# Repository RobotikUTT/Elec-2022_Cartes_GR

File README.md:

# Elec-2022_Cartes_GR

Circuits imprimés pour le Gros Robot de la Coupe de France de Robotique 2022

## PCB Arduino Mega (PCB_Mega)
Shield pour Arduino Mega 2560.
Alimentée en 5V par un bornier à vis.

**Comprends :**
- Port série pour la communication avec la Nano
- Ports séries Servos (XL320 + AX-12A)
- Sorties logiques moteurs roues
- Sorties pompes à vide
- Entrées Roues Codeuses
- Entrées analogiques courant pompes à vide
- Entrées Tirette et Interrupteur de sélection du côté
- Leds de Status Rouge, Verte et Bleue
- 10 GPIO supplémentaires non-utilisés

___

## PCB Arduino Nano (PCB_Nano)
Module hôte pour Arduino Nano.
Alimentée en 5V par un bornier à vis.

**Comprends :**
- Port série pour communication avec la Mega
- Port I2C pour écran LCD
- Entrées/Sorties Echos et Triggers pour les sonars
- 6 GPIO supplémentaires non-utilisés

## PCB Alimentation (PCB_Power)
Module d'alimentation pour le Gros Robot.

**Rails fournis :**
- 5V (2A max) : Arduinos Mega et Nano, pompes à vide et écran LCD.
- Vbat : Moteurs roues et modules Step-Down pour les Servos
(Vbat correspond à Bat+ en série avec un Fusible de 5A et le BAU)

**Comprends :**
- Connecteur arrivée de la batterie (Bat+/Bat-)
- Connecteur Bouton Arrêt d'Urgence (BAU)
- 3 sorties Vbat
- 3 sorties 5V
- 7 sorties GND (<=> Bat-)

___

## Screenshots

### PCB_Mega

### PCB_Nano

### PCB_Power

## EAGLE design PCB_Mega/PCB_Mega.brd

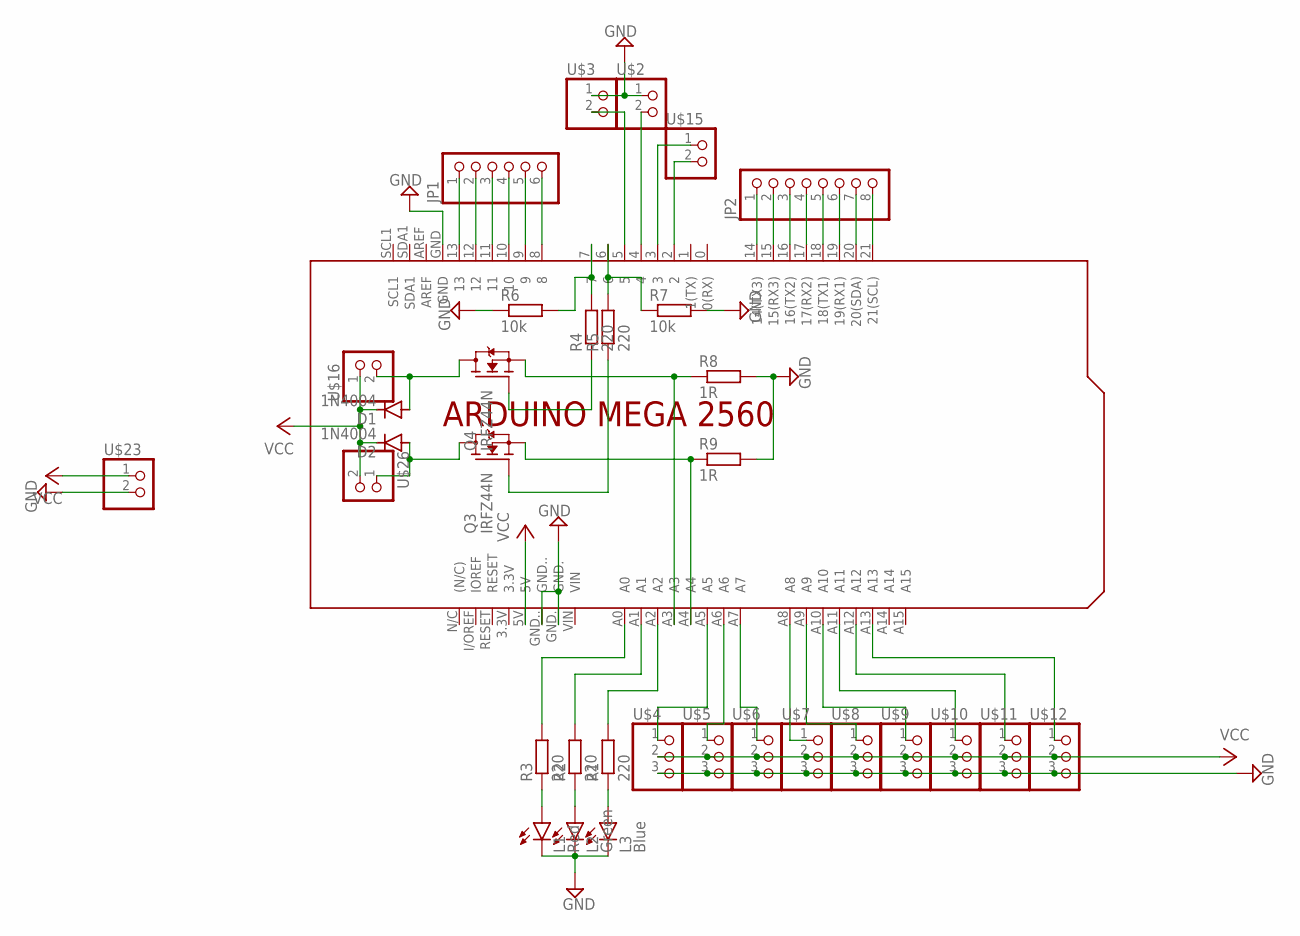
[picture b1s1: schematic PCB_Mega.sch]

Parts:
D1, D2: 1N4004; DO41-10
JP1: PINHD-1X6; 1X06
JP2: PINHD-1X8; 1X08
L1: Red; LED3MM
L2: Green; LED3MM
L3: Blue; LED3MM
Q3, Q4: IRFZ44N; TO220V
R1, R2, R3, R4, R5: 220; 0207/7-OFFSET
R6, R7: 10k; 0207/7-OFFSET
R8, R9: 1R; 10/28-90
U$1: ARDUINO_MEGA2560_SHIELD_NO_LOWER
U$2, U$3, U$15: PINHD-1X2; 1X02
U$4, U$5, U$6, U$7, U$8, U$9, U$10, U$11, U$12: PINHD-1X3; 1X03
U$16, U$23, U$26: TERMINALBLOCK_1X2-5.0MM

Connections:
GND: L1.K (C), L2.K (C), L3.K (C), R6.1, R7.2, R8.P$2 (2), R9.P$2 (2), U$1.GND, U$1.GND., U$1.GND.., U$2.1, U$3.1, U$4.3, U$5.3, U$6.3, U$7.3, U$8.3, U$9.3, U$10.3, U$11.3, U$12.3, U$23.2
unnamed: U$1.A5, U$4.1
unnamed: U$1.A6, U$5.1
unnamed: U$1.A7, U$6.1
unnamed: U$1.A8, U$7.1
unnamed: U$1.A9, U$8.1
unnamed: U$1.A10, U$9.1
unnamed: U$1.A11, U$10.1
unnamed: U$1.A12, U$11.1
unnamed: U$1.A13, U$12.1
unnamed: JP1.1, U$1.13
unnamed: JP1.2, U$1.12
unnamed: JP1.3, U$1.11
unnamed: JP1.4, U$1.10
unnamed: JP1.5, U$1.9
unnamed: U$1.5, U$3.2
unnamed: U$1.4, U$2.2
unnamed: JP2.1, U$1.14 (14(TX3))
unnamed: JP2.2, U$1.15 (15(RX3))
unnamed: U$1.3, U$15.1
unnamed: U$1.2, U$15.2
unnamed: JP1.6, U$1.8
unnamed: JP2.3, U$1.16 (16(TX2))
unnamed: JP2.4, U$1.17 (17(RX2))
unnamed: JP2.5, U$1.18 (18(TX1))
unnamed: D1.A, Q4.2 (D), U$16.2
unnamed: R4.2, R6.2, U$1.7
unnamed: R5.2, R7.1, U$1.6
unnamed: D2.A, Q3.2 (D), U$26.1
unnamed: JP2.6, U$1.19 (19(RX1))
unnamed: JP2.7, U$1.20 (20(SDA))
unnamed: JP2.8, U$1.21 (21(SCL))
unnamed: Q3.1 (G), R5.1
unnamed: Q4.1 (G), R4.1
unnamed: L1.A, R3.1
unnamed: L2.A, R2.1
unnamed: L3.A, R1.1
unnamed: R1.2, U$1.A2
unnamed: R2.2, U$1.A1
unnamed: R3.2, U$1.A0
unnamed: Q3.3 (S), R9.P$1 (1), U$1.A4
unnamed: Q4.3 (S), R8.P$1 (1), U$1.A3
VCC: D1.C, D2.C, U$1.5V, U$4.2, U$5.2, U$6.2, U$7.2, U$8.2, U$9.2, U$10.2, U$11.2, U$12.2, U$16.1, U$23.1, U$26.2

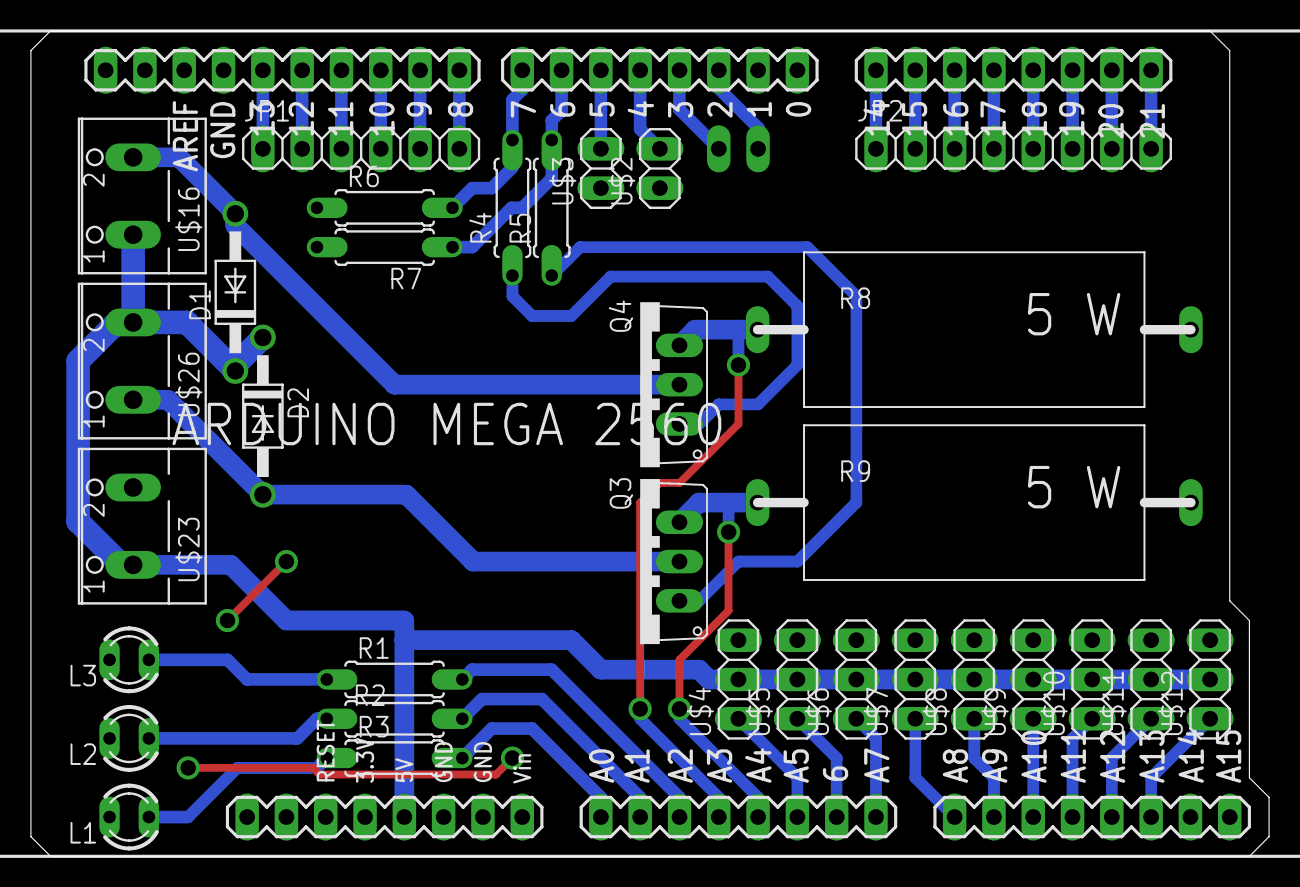
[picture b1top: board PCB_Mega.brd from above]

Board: 2 copper layers, 80.0 x 53.3 mm, 34 parts (1 on the bottom side), 43 nets.

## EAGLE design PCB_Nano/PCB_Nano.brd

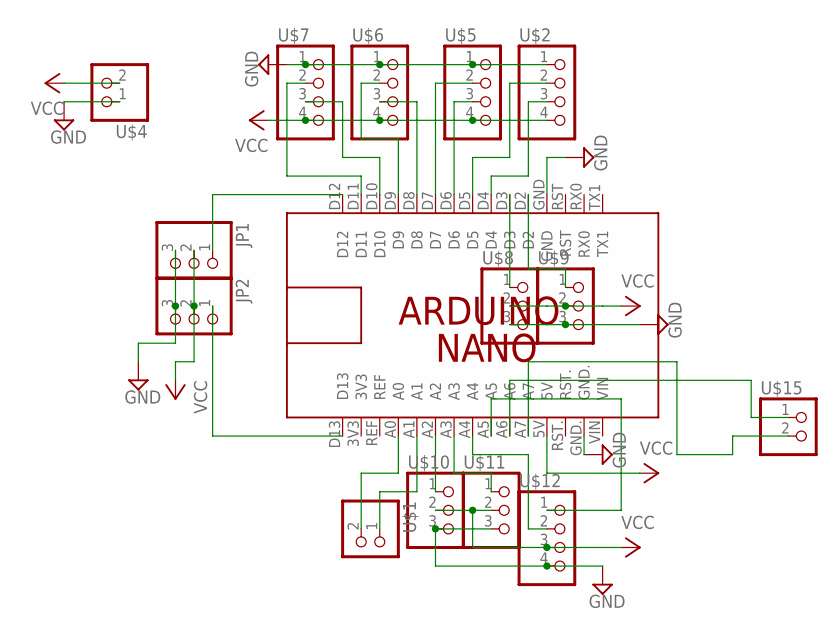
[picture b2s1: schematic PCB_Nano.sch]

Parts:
JP1, JP2: PINHD-1X3; 1X03
PCB1: ARDUINO_NANO_SHIELD; ARDUINO_NANO_W_HEADER_&_SOCKET
U$1, U$15: PINHD-1X2; 1X02
U$2, U$5, U$6, U$7, U$12: PINHD-1X4; 1X04
U$4: TERMINALBLOCK_1X2-5.0MM
U$8, U$9, U$10, U$11: PINHD-1X3; 1X03

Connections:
GND: JP1.3, JP2.3, PCB1.GND, PCB1.GND., U$2.1, U$4.1, U$5.1, U$6.1, U$7.1, U$8.3, U$9.3, U$10.3, U$11.3, U$12.4
unnamed: PCB1.D4, U$2.3
unnamed: PCB1.D5, U$2.2
unnamed: PCB1.D6, U$5.3
unnamed: PCB1.D7, U$5.2
unnamed: PCB1.D8, U$6.3
unnamed: PCB1.D9, U$6.2
unnamed: PCB1.D10, U$7.3
unnamed: PCB1.D11, U$7.2
unnamed: PCB1.A1, U$1.1
unnamed: PCB1.A0, U$1.2
unnamed: PCB1.D3, U$8.1
unnamed: PCB1.D2, U$9.1
unnamed: JP1.1, PCB1.D12
unnamed: JP2.1, PCB1.D13
unnamed: PCB1.A2, U$10.1
unnamed: PCB1.A3, U$11.1
unnamed: PCB1.A4, U$12.2
unnamed: PCB1.A5, U$12.1
unnamed: PCB1.A6, U$15.1
unnamed: PCB1.A7, U$15.2
VCC: JP1.2, JP2.2, PCB1.5V, U$2.4, U$4.2, U$5.4, U$6.4, U$7.4, U$8.2, U$9.2, U$10.2, U$11.2, U$12.3

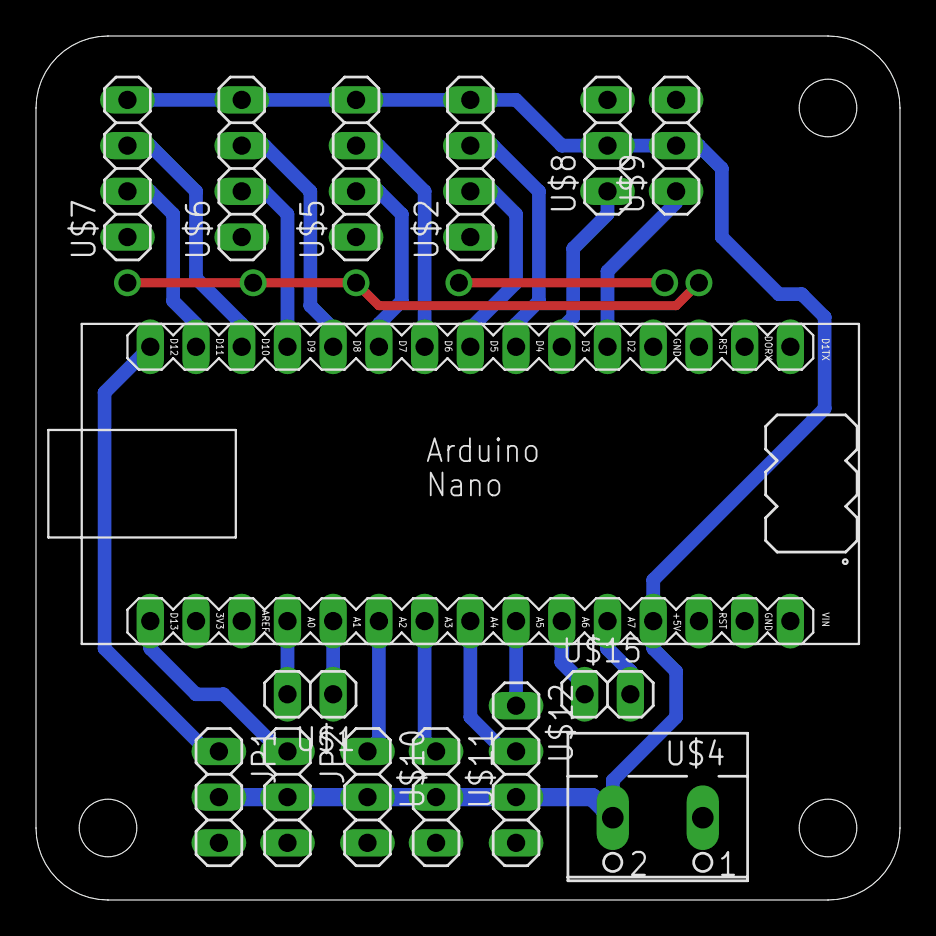
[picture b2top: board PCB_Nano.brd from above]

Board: 2 copper layers, 48.0 x 48.0 mm, 15 parts (0 on the bottom side), 22 nets.

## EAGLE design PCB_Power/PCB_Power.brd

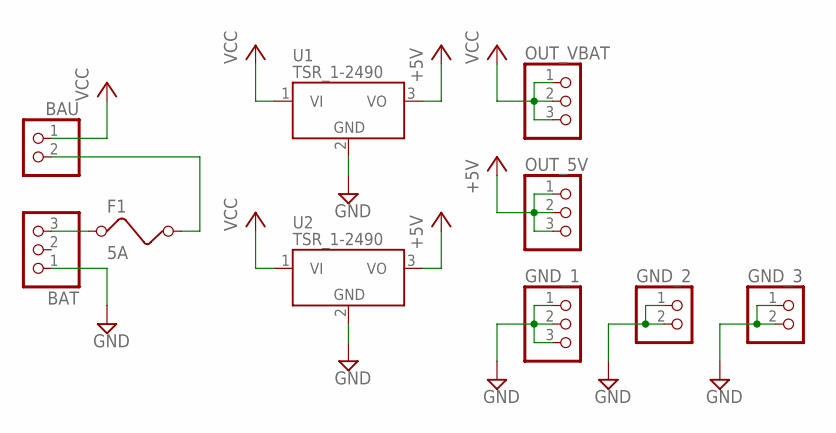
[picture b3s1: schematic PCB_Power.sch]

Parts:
BAT: TERMINALBLOCK_1X3-5.0MM
BAU: TERMINALBLOCK_1X2-5.0MM
F1: 5A; FUSE
GND_1: TERMINALBLOCK_1X3-5.0MM
GND_2, GND_3: TERMINALBLOCK_1X2-5.0MM
OUT_5V: TERMINALBLOCK_1X3-5.0MM
OUT_VBAT: TERMINALBLOCK_1X3-5.0MM
U1, U2: TSR_1-2490; TSR-1

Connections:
+5V: OUT_5V.1, OUT_5V.2, OUT_5V.3, U1.3 (VO), U2.3 (VO)
B_IN: BAT.3, F1.1
F: BAU.2, F1.2
GND: BAT.1, GND_1.1, GND_1.2, GND_1.3, GND_2.1, GND_2.2, GND_3.1, GND_3.2, U1.2 (GND), U2.2 (GND)
VCC: BAU.1, OUT_VBAT.1, OUT_VBAT.2, OUT_VBAT.3, U1.1 (VI), U2.1 (VI)

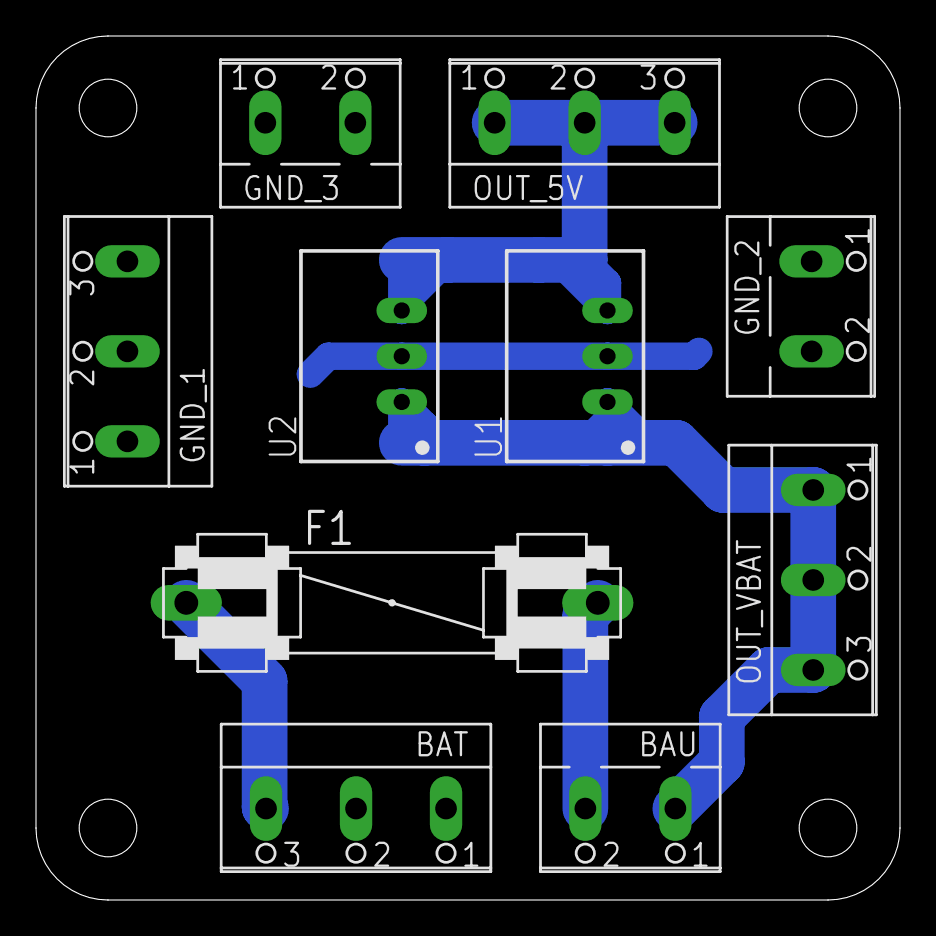
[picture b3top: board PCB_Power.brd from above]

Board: 2 copper layers, 48.0 x 48.0 mm, 10 parts (0 on the bottom side), 5 nets.

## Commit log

2022-05-21 Added all PCBs
2022-05-21 Added Screenshots
